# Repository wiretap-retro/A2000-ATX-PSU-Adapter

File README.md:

# A2000 ATX PSU Adapter
A power supply adapter for the Amiga 2000 to use an ATX power supply -- also provides -5VDC, 5V & 12V fan headers.

\

## Assembly
* Order the board from your PCB fabricator of choice. (JLCPCB, PCBway, OSH Park, etc.)
* Order the parts per the BOM. (Mouser, Digikey, RS, etc.)
* Solder the D1 and R1 first. (optional, for ATX "power good" signal indication)
* Solder C1 and C2 capacitors.
* Install U1 through the board, bend over the leads, flush clip them, then solder.
* Solder J1, then J2.
* Solder the power switch pin header and the fan headers.

## Installation
* Install an ATX power supply in your Amiga 2000. This step is not covered here, as there are many tutorials online already. Do not cut the 20-pin/24-pin connector.
* Set motherboard jumper U300 for using the Vsync generated TICK signal.
* Plug the A2000 ATX PSU Adapter into the motherboard's power connector.
* Plug in a toggle switch or latching switch to the 2-pin PWRSW pin header. The button can be mounted anywhere you run the wires to, or you can also use the original power supply's rocker switch to keep the OEM look and feel. You can also install a jumper here, if you want to utilize your ATX/SFX power supply rocker switch in the case of just plopping the power supply on the desk or modding the case to mount the whole thing in there.
* Connect your ATX power supply 20-pin/24-pin connector to your newly built power adapter.
* Optional: The board provides 5V and 12V fan headers to cool anything you want. For example, the 5V fan header is good for a Raspberry Pi fan for the PiSTORM.

## Notes
* The 7905 voltage regulator takes power from the -12VDC ATX power supply and converts it to -5VDC for the Amiga. It is capable of providing plenty of power, and is overkill. Your ATX power supply -12VDC rail will tap out well before the abilities of the 7905.
* This ATX power supply adapter will probably be a little difficult to remove since it is a 14-pin connector with high friction. Be careful if you remove it. I designed it with the edges protruding a little so you have something to grip. Insertion/removal may be easier if the ATX power supply is already connected since you'll have additional plastic to grab onto. A slight rocking motion will help get the connector over the bump.
* This is a 4-layer board with the inner planes being 5V and 12V. I increased the width of the thermal reliefs to allow sufficient current to pass, so soldering will be a little more difficult due to heat transfer to the large planes. Use a larger tip and a higher temperature when soldering to make sure the fillets look nice and no dry solder joints occur.

## Revision Info
* Rev 1: Changed power indication LED from the PG pin to a 5V source. The PG pin only stays high for about 5 seconds depending on the power supply.
* Rev 0: Initial revision.

## Misc
* This design is open source. Feel free to do what you want with it.
* Design adapted from my PICO-AT power adapter.

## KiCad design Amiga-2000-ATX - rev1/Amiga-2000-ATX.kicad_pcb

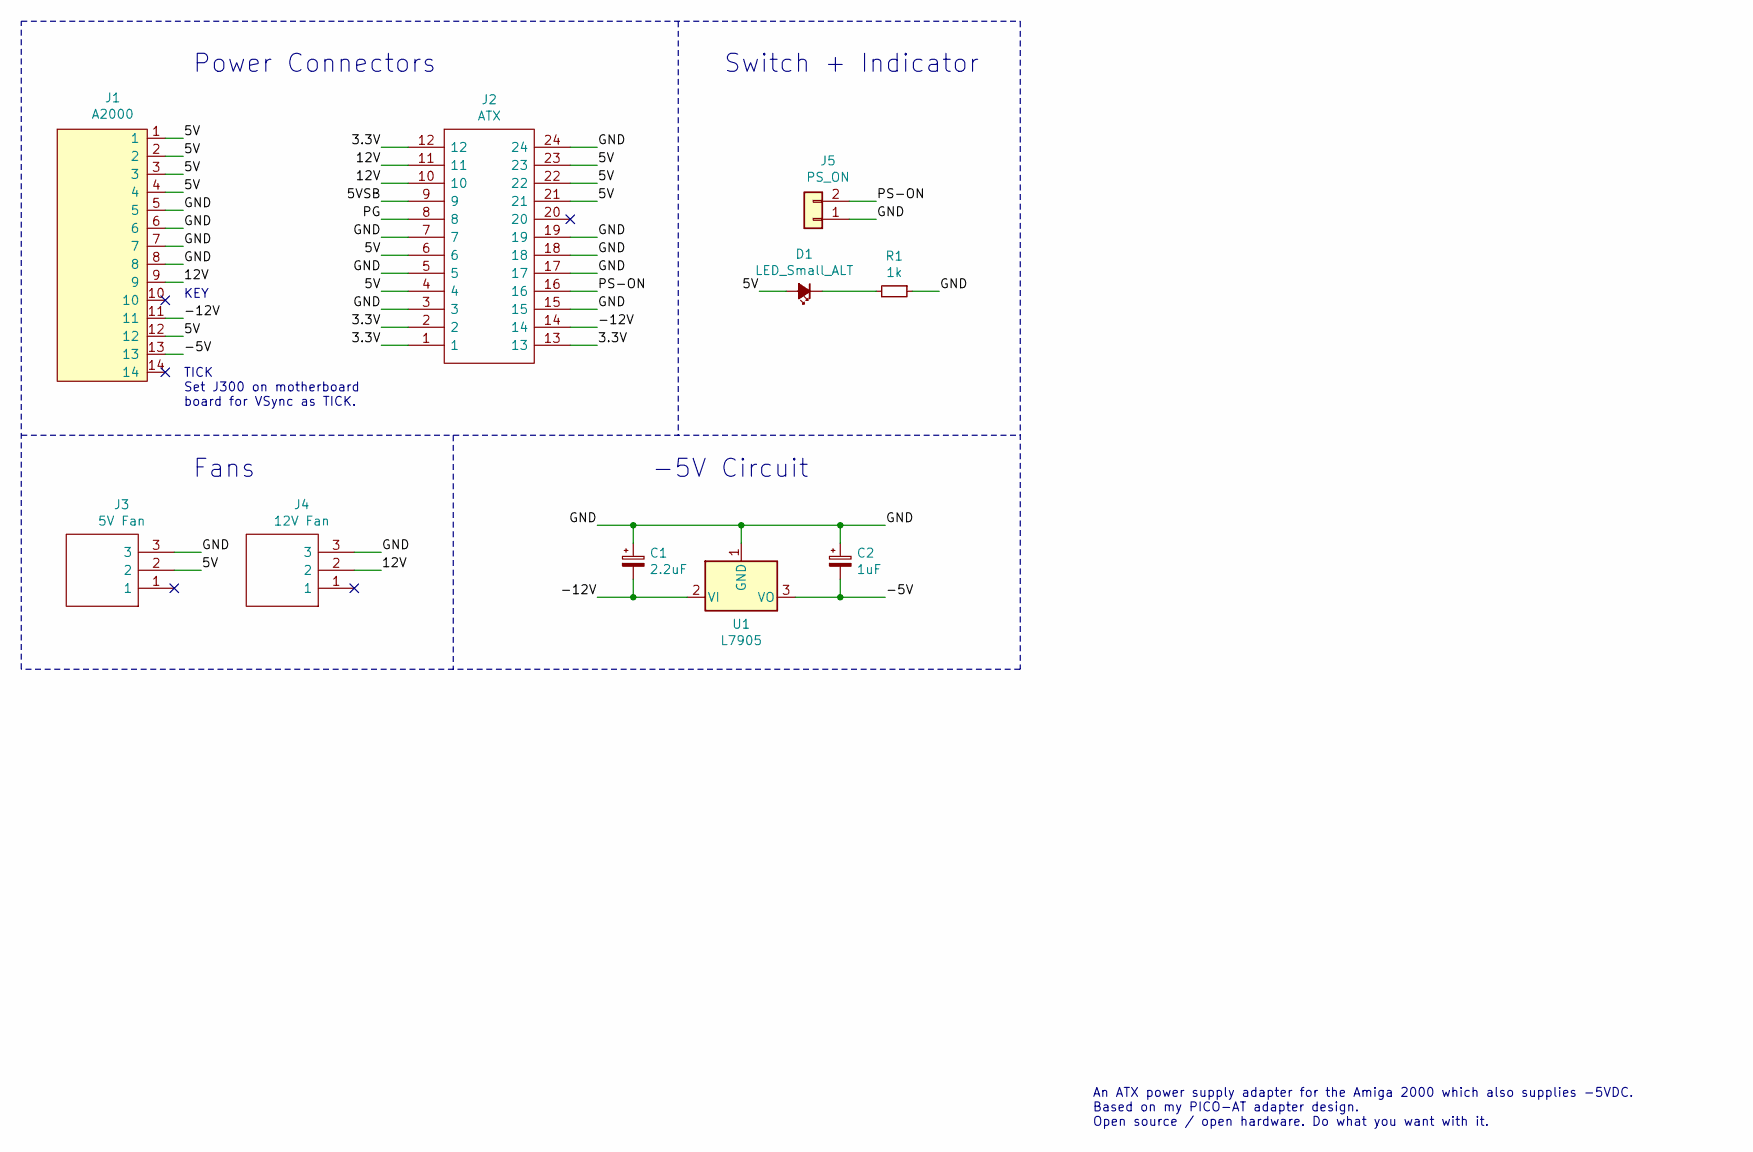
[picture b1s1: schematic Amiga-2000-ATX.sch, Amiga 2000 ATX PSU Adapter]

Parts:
C1: 2.2uF; CP_EIA-6032-28_Kemet-C_Pad2.25x2.35mm_HandSolder
C2: 1uF; CP_EIA-6032-28_Kemet-C_Pad2.25x2.35mm_HandSolder
D1: LED_Small_ALT; LED_0805_2012Metric_Castellated
J1: A2000; 09481164
J2: ATX; 87427-2402; Mouser Part Number 538-87427-2402
J3: 5V Fan; SHDR3W82P0X254_1X3_747X635X818P; Mouser Part Number 538-22-23-2031
J4: 12V Fan; SHDR3W82P0X254_1X3_747X635X818P; Mouser Part Number 538-22-23-2031
J5: PS_ON; PinHeader_1x02_P2.54mm_Vertical
R1: 1k; R_0805_2012Metric_Pad1.15x1.40mm_HandSolder
U1: L7905; TO-220-3_Horizontal_TabDown

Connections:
/3.3V: J2.1, J2.2, J2.12, J2.13
/5V: D1.2 (A), J1.1, J1.2, J1.3, J1.4, J1.12, J2.4, J2.6, J2.21, J2.22, J2.23, J3.2
/5VSB: J2.9
/12V: J1.9, J2.10, J2.11, J4.2
/-5V: C2.2, J1.13, U1.3 (VO)
/-12V: C1.2, J1.11, J2.14, U1.2 (VI)
/GND: C1.1, C2.1, J1.5, J1.6, J1.7, J1.8, J2.3, J2.5, J2.7, J2.15, J2.17, J2.18, J2.19, J2.24, J3.3, J4.3, J5.1, R1.1, U1.1 (GND); also elsewhere on the board
/PG: J2.8
/PS-ON: J2.16, J5.2; also elsewhere on the board
unnamed: D1.1 (K), R1.2

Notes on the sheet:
TICK Set J300 on motherboard board for VSync as TICK.
KEY
Fans
Switch + Indicator
-5V Circuit
Power Connectors
An ATX power supply adapter for the Amiga 2000 which also supplies -5VDC. Based on my PICO-AT adapter design. Open source / open hardware. Do what you want with it.

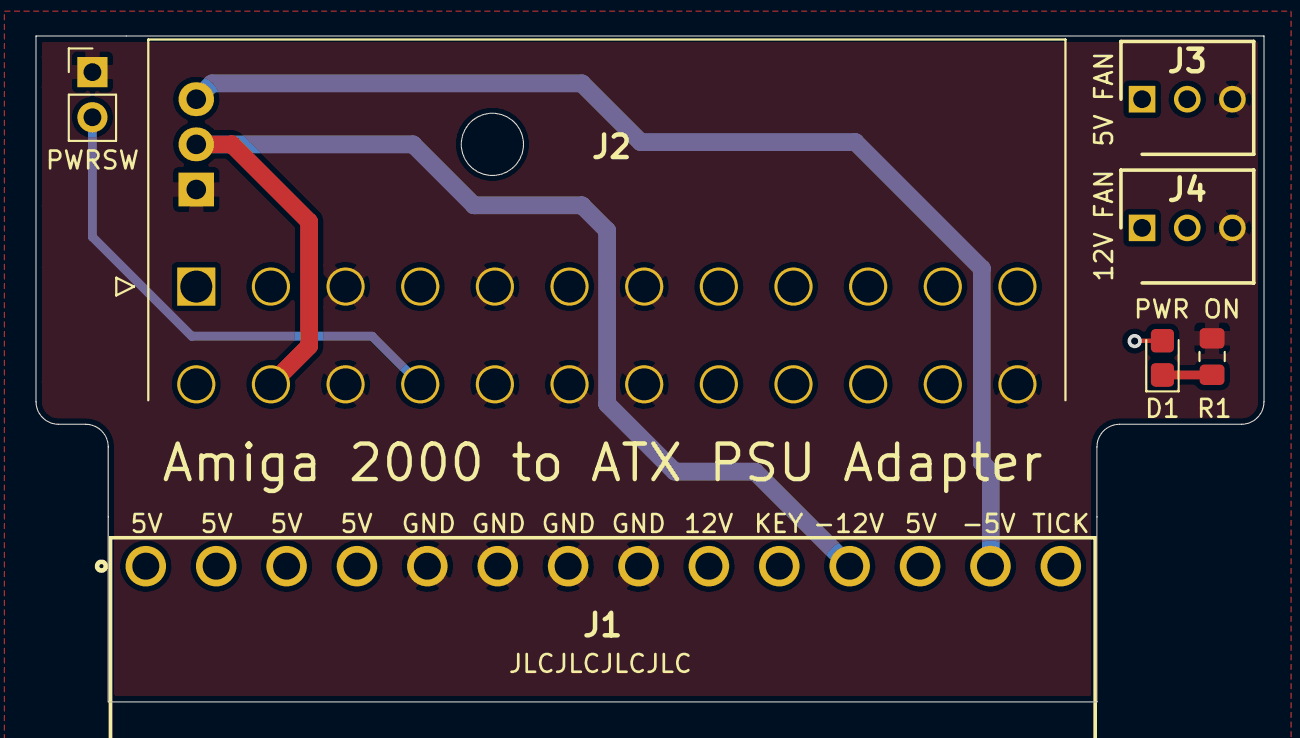
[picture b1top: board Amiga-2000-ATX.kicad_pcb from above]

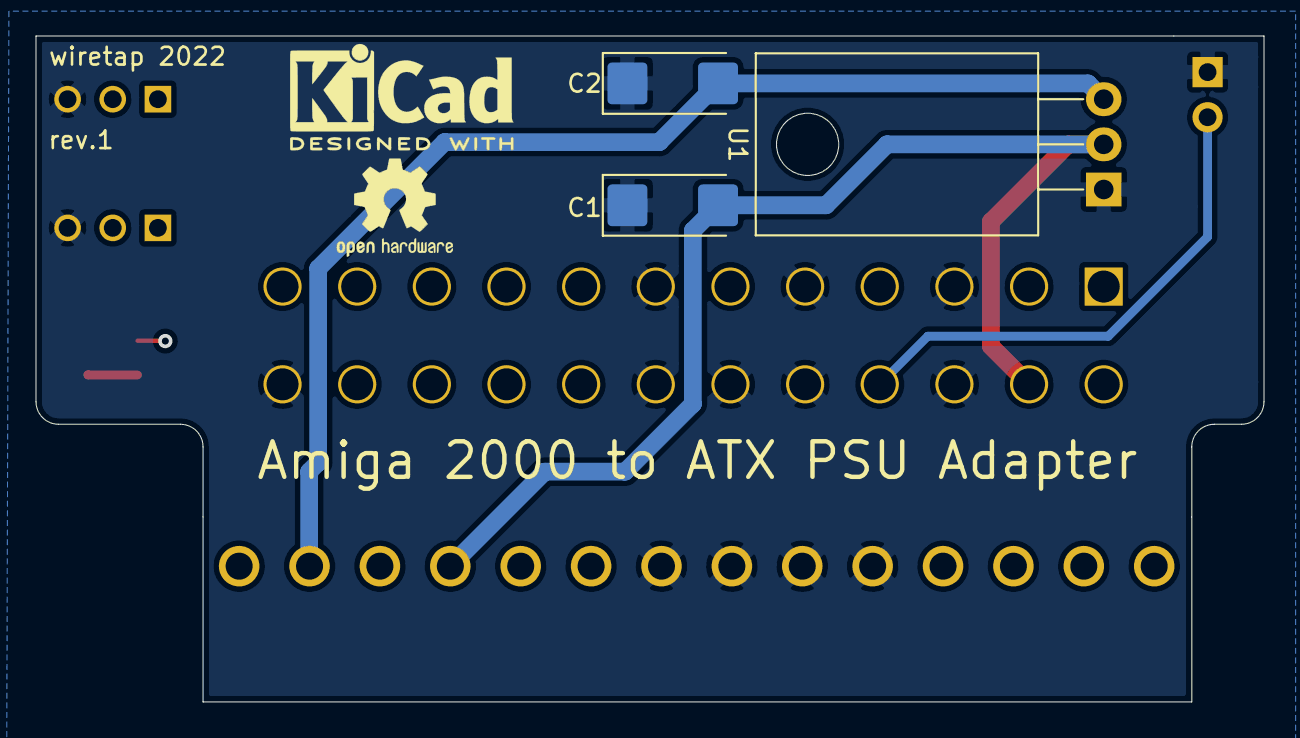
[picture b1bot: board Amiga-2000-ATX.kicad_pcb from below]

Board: 4 copper layers, 69.1 x 37.5 mm, 10 parts (3 on the bottom side), 8 nets.

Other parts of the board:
PWRSW: PS_ON; PinHeader_1x02_P2.54mm_Vertical

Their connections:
/GND: PWRSW.1; also elsewhere on the board
/PS-ON: PWRSW.2; also elsewhere on the board
